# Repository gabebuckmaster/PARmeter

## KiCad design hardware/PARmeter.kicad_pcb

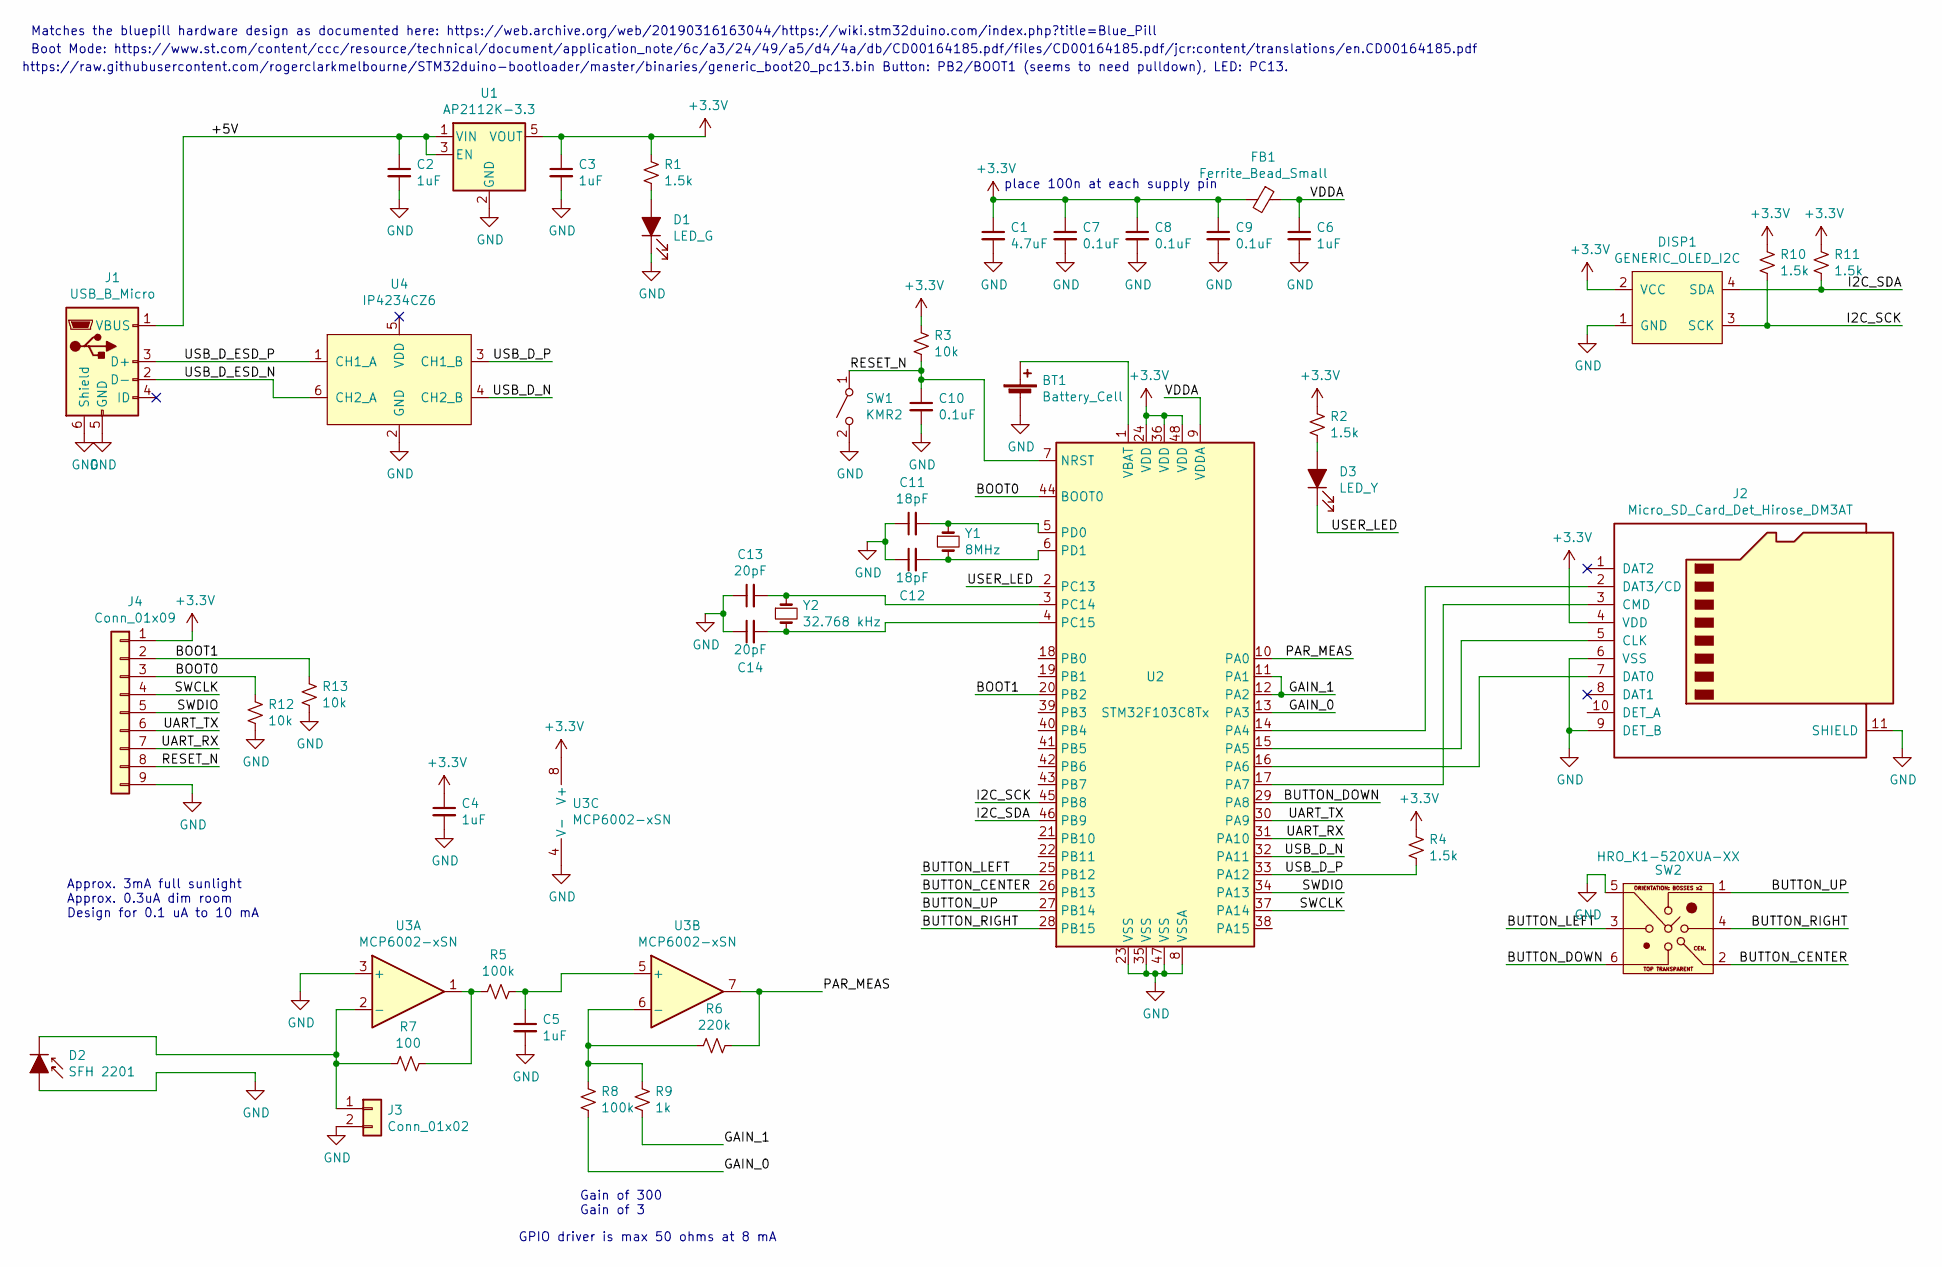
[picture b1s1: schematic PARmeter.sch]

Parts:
BT1: Battery_Cell; BatteryHolder_Keystone_3000_1x12mm
C1: 4.7uF; C_0805_2012Metric
C2, C3, C4, C5, C6: 1uF; C_0805_2012Metric
C7, C8, C9, C10: 0.1uF; C_0805_2012Metric
C11, C12: 18pF; C_0805_2012Metric
C13, C14: 20pF; C_0805_2012Metric
D1: LED_G; LED_0805_2012Metric
D2: SFH 2201; OSRAM_SFH2201
D3: LED_Y; LED_0805_2012Metric
DISP1: GENERIC_OLED_I2C; Generic_OLED_Display_0.96
FB1: Ferrite_Bead_Small; LED_0805_2012Metric
J1: USB_B_Micro; USB_Micro-B_Amphenol_10118194-0001LF_Horizontal
J2: Micro_SD_Card_Det_Hirose_DM3AT; microSD_HC_Hirose_DM3AT-SF-PEJM5
J3: Conn_01x02; PinHeader_1x02_P2.54mm_Vertical
J4: Conn_01x09; PinHeader_1x09_P2.54mm_Vertical
R1, R2, R4, R10, R11: 1.5k; R_0805_2012Metric
R3, R12, R13: 10k; R_0805_2012Metric
R5, R8: 100k; R_0805_2012Metric
R6: 220k; R_0805_2012Metric
R7: 100; R_0805_2012Metric
R9: 1k; R_0805_2012Metric
SW1: KMR2; SW_Push_1P1T_NO_CK_KMR2
SW2: HRO_K1-520XUA-XX
U1: AP2112K-3.3; SOT-23-5
U2: STM32F103C8Tx; LQFP-48_7x7mm_P0.5mm
U3: MCP6002-xSN; SOIC-8_3.9x4.9mm_P1.27mm
U4: IP4234CZ6; TSOP-6_1.65x3.05mm_P0.95mm
Y1: 8MHz; Crystal_SMD_5032-2Pin_5.0x3.2mm
Y2: 32.768 kHz; Crystal_SMD_3215-2Pin_3.2x1.5mm

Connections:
+3V3: C1.1, C3.1, C4.1, C7.1, C8.1, C9.1, DISP1.2 (VCC), FB1.2, J2.4 (VDD), J4.1, R1.1, R2.1, R3.1, R4.2, R10.2, R11.2, U1.5 (VOUT), U2.24 (VDD), U2.36 (VDD), U2.48 (VDD), U3.8 (V+)
/+5V: C2.1, J1.1 (VBUS), U1.1 (VIN), U1.3 (EN)
/BOOT0: J4.3, R12.1, U2.44 (BOOT0)
/BOOT1: J4.2, R13.1, U2.20 (PB2)
/BUTTON_CENTER: SW2.2, U2.26 (PB13)
/BUTTON_DOWN: SW2.6, U2.29 (PA8)
/BUTTON_LEFT: SW2.3, U2.25 (PB12)
/BUTTON_RIGHT: SW2.4, U2.28 (PB15)
/BUTTON_UP: SW2.1, U2.27 (PB14)
/GAIN_0: R8.2, U2.13 (PA3)
/GAIN_1: R9.2, U2.11 (PA1), U2.12 (PA2)
/I2C_SCK: DISP1.3 (SCK), R10.1, U2.45 (PB8)
/I2C_SDA: DISP1.4 (SDA), R11.1, U2.46 (PB9)
/PAR_MEAS: R6.1, U2.10 (PA0), U3.7
/RESET_N: C10.1, J4.8, R3.2, SW1.1 (A), U2.7 (NRST)
/SWCLK: J4.4, U2.37 (PA14)
/SWDIO: J4.5, U2.34 (PA13)
/UART_RX: J4.7, U2.31 (PA10)
/UART_TX: J4.6, U2.30 (PA9)
/USB_D_ESD_N: J1.2 (D-), U4.6 (CH2_A)
/USB_D_ESD_P: J1.3 (D+), U4.1 (CH1_A)
/USB_D_N: U2.32 (PA11), U4.4 (CH2_B)
/USB_D_P: R4.1, U2.33 (PA12), U4.3 (CH1_B)
/USER_LED: D3.1 (K), U2.2 (PC13)
/VDDA: C6.1, FB1.1, U2.9 (VDDA)
GND: BT1.2 (-), C1.2, C2.2, C3.2, C4.2, C5.2, C6.2, C7.2, C8.2, C9.2, C10.2, C11.1, C12.1, C13.1, C14.1, D1.1 (K), D2.2 (A), DISP1.1 (GND), J1.5 (GND), J1.6 (Shield), J2.6 (VSS), J2.9 (DET_B), J2.11 (SHIELD), J3.2, J4.9, R12.2, R13.2, SW1.2 (B), SW2.5, U1.2 (GND), U2.8 (VSSA), U2.23 (VSS), U2.35 (VSS), U2.47 (VSS), U3.3 (+), U3.4 (V-), U4.2 (GND)
unnamed: BT1.1 (+), U2.1 (VBAT)
unnamed: C5.1, R5.1, U3.5 (+)
unnamed: C11.2, U2.5 (PD0), Y1.1
unnamed: C12.2, U2.6 (PD1), Y1.2
unnamed: C13.2, U2.3 (PC14), Y2.1
unnamed: C14.2, U2.4 (PC15), Y2.2
unnamed: D1.2 (A), R1.2
unnamed: D2.1 (K), J3.1, R7.2, U3.2 (-)
unnamed: D3.2 (A), R2.2
unnamed: J2.2 (DAT3/CD), U2.14 (PA4)
unnamed: J2.3 (CMD), U2.17 (PA7)
unnamed: J2.5 (CLK), U2.15 (PA5)
unnamed: J2.7 (DAT0), U2.16 (PA6)
unnamed: R5.2, R7.1, U3.1
unnamed: R6.2, R8.1, R9.1, U3.6 (-)

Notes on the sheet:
Matches the bluepill hardware design as documented here: https://web.archive.org/web/20190316163044/https://wiki.stm32duino.com/index.php?title=Blue_Pill
Approx. 3mA full sunlight Approx. 0.3uA dim room Design for 0.1 uA to 10 mA
Gain of 300 Gain of 3
GPIO driver is max 50 ohms at 8 mA
place 100n at each supply pin
Boot Mode: https://www.st.com/content/ccc/resource/technical/document/application_note/6c/a3/24/49/a5/d4/4a/db/CD00164185.pdf/files/CD00164185.pdf/jcr:content/translations/en.CD00164185.pdf
https://raw.githubusercontent.com/rogerclarkmelbourne/STM32duino-bootloader/master/binaries/generic_boot20_pc13.bin Button: PB2/BOOT1 (seems to need pulldown), LED: PC13.

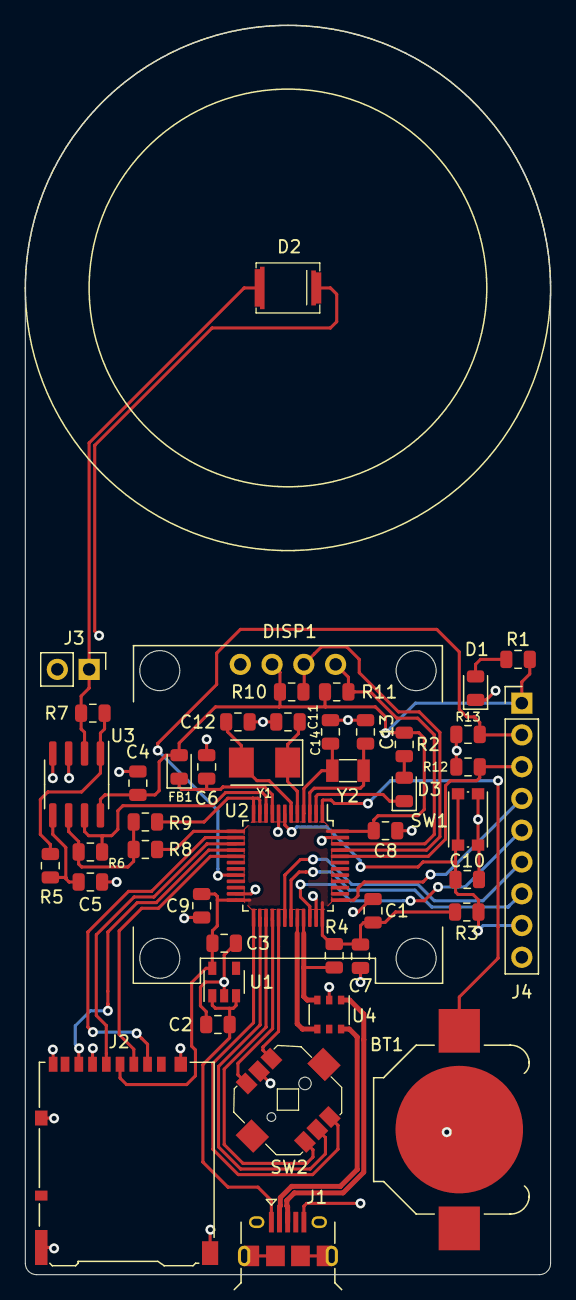
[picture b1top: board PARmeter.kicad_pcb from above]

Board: 2 copper layers, 42.0 x 99.9 mm, 45 parts (0 on the bottom side), 41 nets.

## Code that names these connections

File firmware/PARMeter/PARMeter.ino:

// Compiled with Generic STM32F1 Series (BluePill F103C8) from STM32 Cores by STMicroelectronics V1.8.0
// Available at: https://github.com/stm32duino/BoardManagerFiles/raw/master/STM32/package_stm_index.json

#include <Arduino.h>
#include <Wire.h>
#include <SPI.h>
#include <SD.h>
#include <U8g2lib.h>

U8G2_SSD1306_128X64_NONAME_F_HW_I2C u8g2(U8G2_R0, /* reset=*/ U8X8_PIN_NONE);

#define DISPLAY_WIDTH 128
#define USER_LED PC13
#define N_AVERAGES 128
#define LOOP_DELAY 100

#define BUTTON_UP_N PB14
#define BUTTON_DOWN_N PA8
#define BUTTON_LEFT_N PB12
#define BUTTON_RIGHT_N PB15
#define BUTTON_CENTER_N PB13

char string_buffer[64];

uint32_t offset_calibration;

void setup(void) 
{
  analogReadResolution(12);
  Wire.setSDA(PB9);
  Wire.setSCL(PB8);
  u8g2.begin();

  offset_calibration = 0; 

  // Turn user LED off - bootloader sometimes leaves it on
  pinMode(USER_LED, INPUT);

  // Set up joystick inputs
  pinMode(BUTTON_UP_N, INPUT_PULLUP);
  pinMode(BUTTON_DOWN_N, INPUT_PULLUP);
  pinMode(BUTTON_LEFT_N, INPUT_PULLUP);
  pinMode(BUTTON_RIGHT_N, INPUT_PULLUP);
  pinMode(BUTTON_CENTER_N, INPUT_PULLUP);

  if (!SD.begin(PA4)) 
  {
    //Serial.println("initialization failed!");
  }
}

void loop(void) 
{
  uint64_t loop_end = millis() + LOOP_DELAY;


  // Get the display buffer ready and draw the units
  u8g2.clearBuffer();
  u8g2.setFont(u8g2_font_9x15_tf);
  u8g2.setFontRefHeightExtendedText();
  u8g2.setDrawColor(1);
  u8g2.setFontPosTop();
  u8g2.setFontDirection(0);
  u8g2.drawStr(DISPLAY_WIDTH/2-u8g2.getStrWidth("\xB5mol/m\xB2s")/2, 42, "\xB5mol/m\xB2s");


  // Calculate ADC counts -> PFD in nmol/m^2s conversion factor
  //https://dammedia.osram.info/media/resource/hires/osram-dam-6303770/SFH%202201_EN.pdf
  // At 550 nm, 0.45 A/W typical
  // 8.1e-6 m^2
  // 3.6e-19 J/photon at 550 nm
  //
  // Iout/(0.45*3.6e-19) = photon flux [photons/sec]
  // Iout/(0.45*3.6e-19)*1/(6.022e23) = photon flux [mol photons/sec]
  // Iout*1/(0.45*3.6e-19)*1/(6.022e23)*1/(8.1e-6) = photon flux [mol photons/sec*m2]
  //
  // [ADC measurement] = 4096*v_meas/3.3
  // [ADC measurement] = 4096*Iout*100*[voltage gain]/3.3
  // Iout = 1/[voltage gain]*3.3/(4096*100)*[ADC measurement]

  // photon flux [umol/m^2s] = 1/[voltage gain]*1e6*1/(0.45*3.6e-19)*1/(6.022e23)*1/(8.1e-6)*3.3/(4096*1000)*[ADC measurement]
  // photon flux [nmol/m^2s]= 1/[voltage gain]*1020*[ADC measurement]
  
  // Take a bunch of measurements for readout stability
  uint32_t measurement_sum = 0;
  for (int i = 0; i < N_AVERAGES; i++)
  {
    measurement_sum += analogRead(PA0);
  }

  // If the center button is pressed, save the current reading as the offset
  if(!digitalRead(BUTTON_CENTER_N))
  {
    offset_calibration = measurement_sum;
  } 

  // Apply offset calibration without causing underflow
  if (measurement_sum > offset_calibration)
  {
    measurement_sum -= offset_calibration;
  }
  else
  {
    measurement_sum = 0;
  }

  // Average and convert to nanomols/m^2s
  uint32_t photon_flux_nmol = measurement_sum/N_AVERAGES*1020;

  // Draw the measured photon flux
  sprintf(string_buffer, "%d", photon_flux_nmol/1000);
  u8g2.setFont(u8g2_font_profont29_tr);
  u8g2.drawStr(DISPLAY_WIDTH/2-u8g2.getStrWidth(string_buffer)/2, 10, string_buffer);

  // for debugging
  //sprintf(string_buffer, "%d", measurement_sum);
  //sprintf(string_buffer, "%d", loop_end-millis()); 
  //u8g2.setFont(u8g2_font_9x15_tf);
  //u8g2.drawStr(0, 0, string_buffer);

  // Send the frame buffer to the display
  u8g2.sendBuffer();

  // Loop delay
  while(millis() < loop_end);
}

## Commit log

2020-01-22 Initial commit
    Hardware design only for now
2020-01-23 Added minimal firmware
    Displays an uncalibrated PAR reading.
2020-01-23 fixed gain values + explicitly set gain outputs
    - Math is hard
    - Shouldn’t be necessary, but doesn’t hurt.
2020-01-23 Ditched dual-gain mode
    There is a problem where the GPIO LOW state pulls to ~3.5mV rather than
    0V as expected due to [supply current] * [resistance between the IC
    ground and PCB ground]. Using superposition, this ~3.5 mV sees an
    inverting amplifier with gain -Rf/Rs and causes an offset in the
    measured value, unfortunately limiting our low-end sensitivity. I
    mitigated this by increasing the transimpedance gain and reducing the
2020-01-23 Disabled center button causing offset calibration by default
    Eventually, would like a real UI for doing calibration (and save the
    values to non-volatile memory). Could be confusing as it was.
2020-01-23 Uncommented center-button offset code
    Turns out the offset varies noticeably between boards.
2020-01-29 Tested micro SD card, confirmed working
    See title
